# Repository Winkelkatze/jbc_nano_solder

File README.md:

# JBC Nano Solder
DIY controller for JBC Nano (NT115) hand piece and C115 tips.

This project can be found on Hackaday: https://hackaday.io/project/175580-diy-jbc-nano-controller

JBC makes awesome high-end soldering irons for professional use. The stations are quite expensive (especially the Nano system), however the tips and hand pieces are reasonably priced for hobby users. Therefore building controllers for these became kind of a sport among DIYers.

## State of the project
This project is in a working state, but is not actively worked on and there are a few unsolved issues, that can lead to the tip overheating if things go wrong. The issues stem from using a low-side gate driver to drive a P-channel FET on the high side. This causes the default state to be **ON**, which in turn means, the heater is powered when there is no signal telling it otherwise. This happens, if the CPU is in RESET or has no power.
Make sure to always disconnect the iron when flashing the firmware, debugging or making changes to the hardware.
**As a mitigation, consider adding a pull-up resistor to the gate driver input.**

## Why Nano and not T245/T210 as everyone else?
The JBC NT115 soldering iron is amazing, it's quite compact, has a slim cable and the grip-to-tip distance is really small. It's meant for super fine-pitched SMT parts, yet if you combine it with a larger tip, its powerful enough for most soldering needs. So, despite being a high precision tool, it is still use-able as a general purpose soldering iron.

Also, there is no real point in DIYing a controller for the larger irons from scratch, since there are already heaps of projects on the internet.

## Differences to the T245/T210
Both have similar tips with the heater and thermocouple embedded directly in the tip.
### Plug
The most obvious difference is the plug, this immediately suggests that there are some more fundamental difference between the two irons.
### Voltage
The NT115 system is designed for a much lower voltage. If I remember correctly, NT115 uses about 9V while T245 is more 20ish. Not sure how bad too much power is, but overloading the tip by a factor of 4 doesn't sound good. For reference, the C115 heaters have a (hot) resistance of about 5 Ohms, which would result in ~16W at 9V, so that's quite close to the nominal 15W of the tips.
### Heater and thermocouple are in series
Despite the cable having three wires and the tip having three contacts, two of the contacts seem to be internally connected inside the tip. So, the only way to power the heater is through the thermocouple. This sounds odd at first, but that's just how it it...

## Status of this project
Everything works pretty well, the heat-up times are JBC-like fast and the temperature is quite stable. I don't know the exact characteristics of the thermocouple, but from tests, I assume the sensitivity is about 9uV/K. It doesn't matter that much, since the temperature you need for a job depends highly on the tip and the job anyway anyway. The hardware supports to measure the supply voltage, but I'm not using it right now.
### Under-voltage self destruct
One issue with the current hardware is a potential self-destruct scenario, if the supply voltage is too low. Since I'm using a low-side driver to drive a high-side P-Channel FET, the undervoltage lockout (about 4V) of the driver will force the FET ON when the supply voltage is too low. This may cause the tip or the mosfet to overheat. So, be careful with the choice of power supply.

## Building the firmware
To build the firmware, you will need the ARM toolchain on your machine. I have only tested the build on Linux, so not sure how this would work on other OSes.
### Clone repo and submodules
```
git clone https://github.com/Winkelkatze/jbc_nano_solder.git
cd jbc_nano_solder
git submodule init
git submodule update
```
### Build libopencm3
```
cd firmware/libopencm3
make
```
### Build the firmware
```
cd firmware
make
```
### Flashing the firmware
You can either use your preferred tool to flash the .elf manually or, if you have openocd installed and the controller connected with a STLINK, the firmware can be flashed with
```
make flash
```

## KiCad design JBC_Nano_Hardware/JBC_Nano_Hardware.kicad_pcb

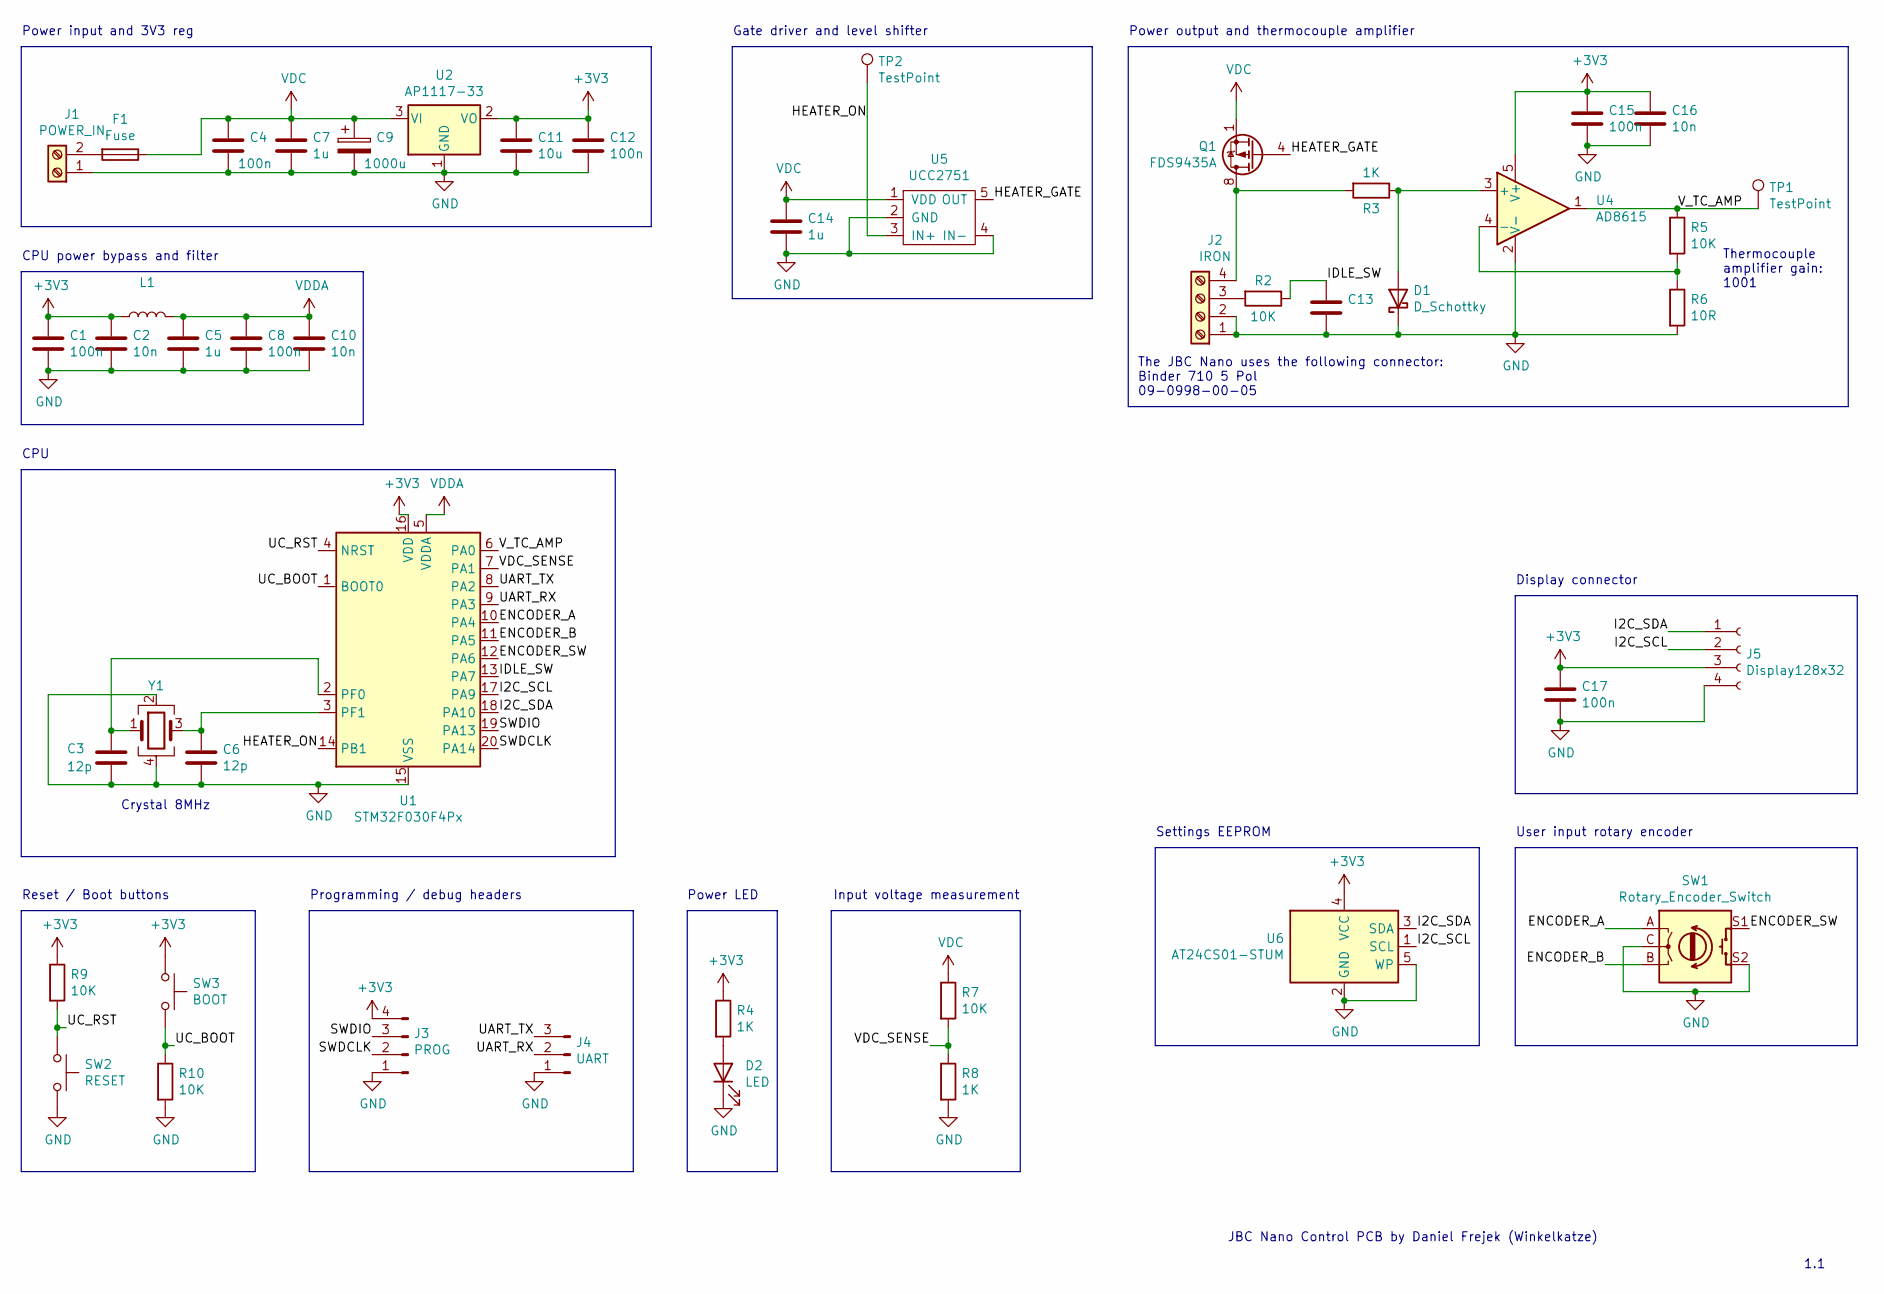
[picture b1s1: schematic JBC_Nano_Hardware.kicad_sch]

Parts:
C1, C4, C8, C12, C15, C17: 100n; C_0603_1608Metric
C2, C10, C16: 10n; C_0603_1608Metric
C3, C6: 12p; C_0603_1608Metric
C5, C7, C14: 1u; C_0603_1608Metric
C9: 1000u; CP_Radial_D10.0mm_P3.50mm
C11: 10u; C_0603_1608Metric
C13: C_0603_1608Metric
D1: D_Schottky; D_0603_1608Metric
D2: LED; LED_0603_1608Metric_Castellated
F1: Fuse; Fuseholder_Cylinder-5x20mm_Schurter_0031_8201_Horizontal_Op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
J1: POWER_IN; TerminalBlock_bornier-2_P5.08mm
J2: IRON; TerminalBlock_bornier-4_P5.08mm
J3: PROG; PinHeader_1x04_P2.54mm_Vertical
J4: UART; PinHeader_1x03_P2.54mm_Vertical
J5: Display128x32; PinSocket_1x04_P2.54mm_Vertical
L1: L_0805_2012Metric
Q1: FDS9435A; SOIC-8_3.9x4.9mm_P1.27mm
R2, R5, R7, R9, R10: 10K; R_0603_1608Metric
R3, R4, R8: 1K; R_0603_1608Metric
R6: 10R; R_0603_1608Metric
SW1: Rotary_Encoder_Switch; RotaryEncoder_Alps_EC12E-Switch_Vertical_H20mm
SW2: RESET; SW_SPST_B3U-1000P
SW3: BOOT; SW_SPST_B3U-1000P
TP1, TP2: TestPoint; TestPoint_Pad_D1.5mm
U1: STM32F030F4Px; TSSOP-20_4.4x6.5mm_P0.65mm
U2: AP1117-33; SOT-223-3_TabPin2
U4: AD8615; TSOT-23-5
U5: UCC2751; SOT-23-5
U6: AT24CS01-STUM; SOT-23-5
Y1: Crystal_GND24; Crystal_SMD_EuroQuartz_MJ-4Pin_5.0x3.2mm

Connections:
+3V3: C1.1, C2.1, C11.1, C12.1, C15.1, C16.1, C17.1, J3.4, J5.3, L1.1, R4.1, R9.1, SW3.1, U1.16 (VDD), U2.2 (VO), U4.5 (V+), U6.4 (VCC)
/ENCODER_A: SW1.A, U1.10 (PA4)
/ENCODER_B: SW1.B, U1.11 (PA5)
/ENCODER_SW: SW1.S1, U1.12 (PA6)
/HEATER_GATE: Q1.4 (G), U5.5 (OUT)
/HEATER_ON: TP2.1, U1.14 (PB1), U5.3 (IN+)
/I2C_SCL: J5.2, U1.17 (PA9), U6.1 (SCL)
/I2C_SDA: J5.1, U1.18 (PA10), U6.3 (SDA)
/IDLE_SW: C13.1, R2.1, U1.13 (PA7)
/SWDCLK: J3.2, U1.20 (PA14)
/SWDIO: J3.3, U1.19 (PA13)
/UART_RX: J4.2, U1.9 (PA3)
/UART_TX: J4.3, U1.8 (PA2)
/UC_BOOT: R10.1, SW3.2, U1.1 (BOOT0)
/UC_RST: R9.2, SW2.1, U1.4 (NRST)
/VDC_SENSE: R7.2, R8.1, U1.7 (PA1)
/V_TC_AMP: R5.1, TP1.1, U1.6 (PA0), U4.1
GND: C1.2, C2.2, C3.2, C4.2, C5.2, C6.2, C7.2, C8.2, C9.2, C10.2, C11.2, C12.2, C13.2, C14.2, C15.2, C16.2, C17.2, D1.1 (K), D2.1 (K), J1.1, J2.1, J2.2, J3.1, J4.1, J5.4, R6.2, R8.2, R10.2, SW1.C, SW1.S2, SW2.2, U1.15 (VSS), U2.1 (GND), U4.2 (V-), U5.2 (GND), U5.4 (IN-), U6.2 (GND), U6.5 (WP), Y1.2, Y1.4
unnamed: C3.1, U1.2 (PF0), Y1.1
unnamed: C6.1, U1.3 (PF1), Y1.3
unnamed: D1.2 (A), R3.1, U4.3 (+)
unnamed: D2.2 (A), R4.2
unnamed: F1.2, J1.2
unnamed: J2.3, R2.2
unnamed: J2.4, Q1.5 (D), Q1.6 (D), Q1.7 (D), Q1.8 (D), R3.2
unnamed: R5.2, R6.1, U4.4 (-)
VDC: C4.1, C7.1, C9.1, C14.1, F1.1, Q1.1 (S), Q1.2 (S), Q1.3 (S), R7.1, U2.3 (VI), U5.1 (VDD)
VDDA: C5.1, C8.1, C10.1, L1.2, U1.5 (VDDA)

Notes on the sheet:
Crystal 8MHz
JBC Nano Control PCB by Daniel Frejek (Winkelkatze)
Reset / Boot buttons
Gate driver and level shifter
CPU
Power LED
Power output and thermocouple amplifier
Thermocouple amplifier gain: 1001
1.1
Settings EEPROM
Input voltage measurement
CPU power bypass and filter
Programming / debug headers
Display connector
Power input and 3V3 reg
The JBC Nano uses the following connector: Binder 710 5 Pol 09-0998-00-05
User input rotary encoder

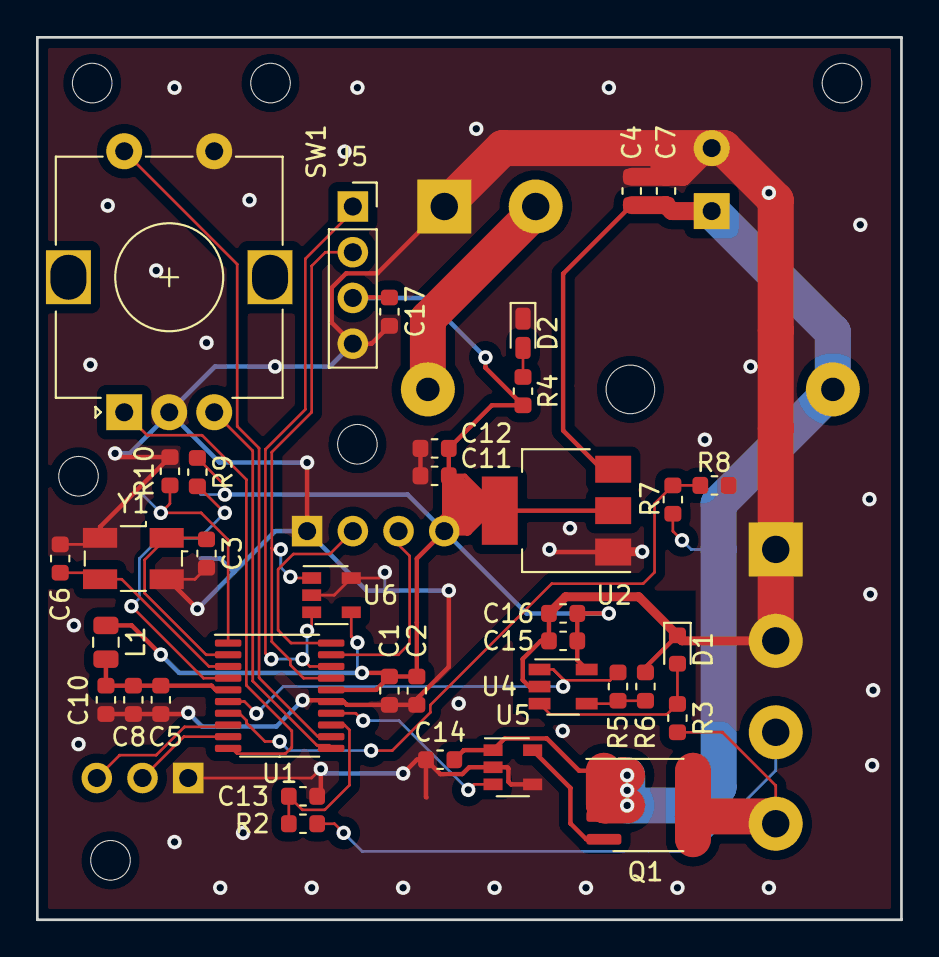
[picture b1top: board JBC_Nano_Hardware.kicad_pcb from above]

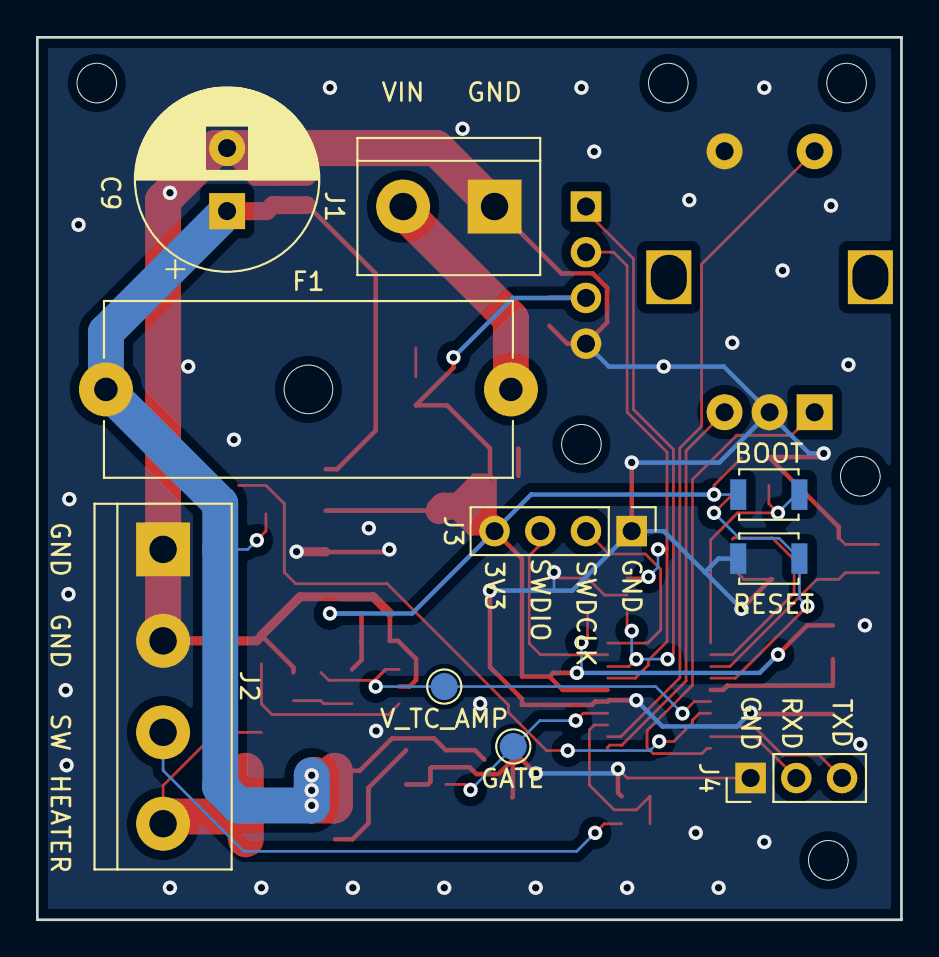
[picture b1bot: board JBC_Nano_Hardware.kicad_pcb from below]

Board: 2 copper layers, 48.0 x 49.0 mm, 47 parts (10 on the bottom side), 28 nets.

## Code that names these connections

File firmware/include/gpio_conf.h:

#pragma once

#include <libopencm3/stm32/gpio.h>
#include <libopencm3/stm32/exti.h>

// GPIOA
#define GPIO_ENCODER_A  GPIO4
#define GPIO_ENCODER_B  GPIO5
#define GPIO_ENCODER_SW GPIO6
#define GPIO_IDLE_SW    GPIO7

// GBIOB
#define GPIO_HEATER     GPIO1

#define EXTI_ENCODER_A  EXTI4
#define EXTI_ENCODER_SW EXTI6
#define EXTI_IDLE_SW    EXTI7

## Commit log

2020-10-11 Added enclosure
2020-10-11 Added pcb
2020-10-11 Fixed hardware issue (wrong mosfet)
2020-10-11 Added schematic as pdf
2020-10-11 added readme
2020-10-11 added holder
2020-10-12 .map shouldn't be in the repo
2020-10-12 replaced window offset with integral component
2020-10-14 better holder arm
2020-10-14 better behaviour of the power button
2020-10-14 A bit more smoothing for the duty display
2020-10-14 clean-up: split into multiple files
2020-10-14 avoid warnings
2020-10-14 avoid warning
2020-10-15 added some more error triggers
2020-10-15 adjust and display temp in 5 deg steps
2020-10-15 Added outlier detection for adc values
2020-10-15 Adapted default value since the controller is much more stable now
2020-10-15 Corrected value for TC sensitivity
2020-10-29 Improved holder arm
2021-01-04 Removed old fabrication output files (never wanted to commit those)
2021-11-17 Missing .gitmodules file
2021-11-17 Added build instructions
2021-11-17 Fixed typo
2021-11-17 Added HAD reference
2021-12-20 Fixed initial config load triggering the watchdog
2021-12-23 Added some more debug output
2021-12-23 Corrected eeprom sizes
2022-09-01 Cleaned schematic and updated to KiCad 6
2022-09-14 Fixed wrong resistor value for thermocouple gain
2022-09-14 Added constant for thermocouple amplifier gain
2025-09-14 Added binary builds
2025-09-14 Added warning to README
